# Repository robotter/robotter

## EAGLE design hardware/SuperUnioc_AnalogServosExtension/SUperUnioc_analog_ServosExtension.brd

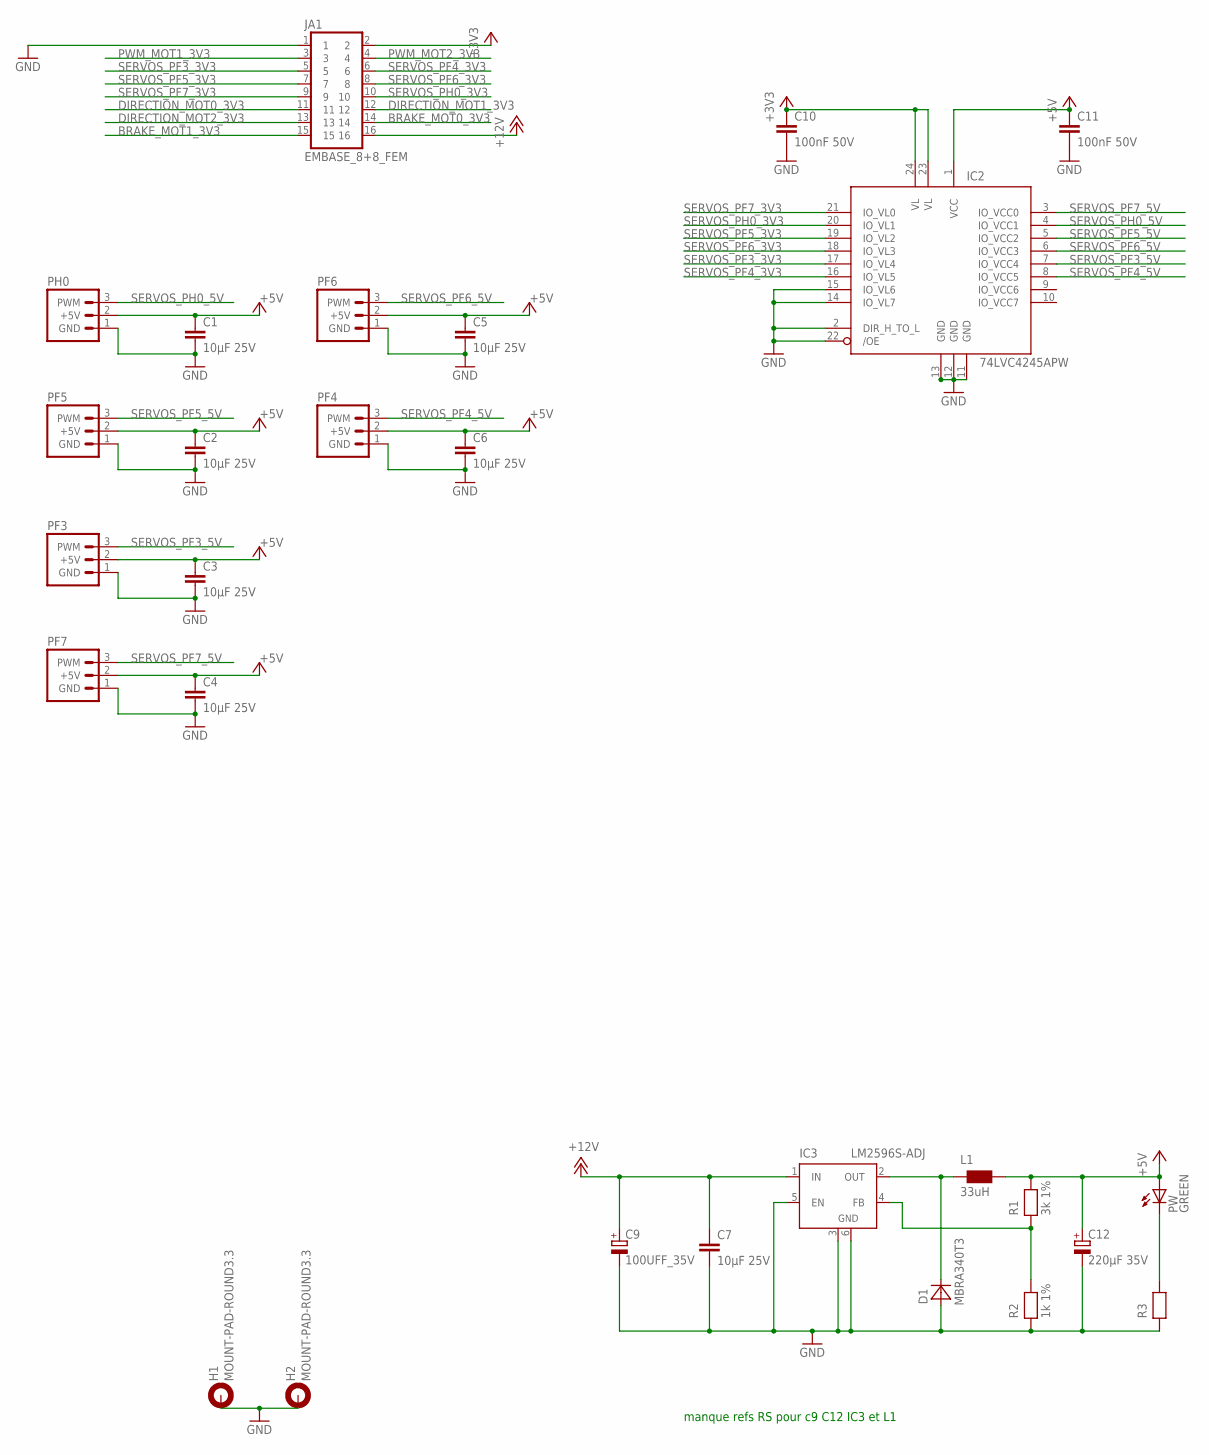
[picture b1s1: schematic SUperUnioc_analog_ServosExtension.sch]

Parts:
C1, C2, C3, C4, C5, C6, C7: 10µF 25V; C1210
C9: 100UFF_35V; PANASONIC_F
C10, C11: 100nF 50V; C0603
C12: 220µF 35V; PANASONIC_F
D1: MBRA340T3; SMA
H1, H2: MOUNT-PAD-ROUND3.3; 3,3-PAD
IC2: 74LVC4245APW; TSSOP24
IC3: LM2596S-ADJ; TO263-5
JA1: EMBASE_8+8_FEM
L1: 33uH; SRR1280
PF3, PF4, PF5, PF6, PF7: ANALOG_SERVO; ANALOG_SERVOS
PH0: ANALOG_SERVO; ANALOG_SERVOS
PW: GREEN; CHIP-LED0805
R1: 3k 1%; R0603
R2: 1k 1%; R0603
R3: 470-F; R0603

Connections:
+3V3: C10.1, IC2.23 (VL), IC2.24 (VL), JA1.2
+5V: C1.1, C2.1, C3.1, C4.1, C5.1, C6.1, C11.1, C12.+, IC2.1 (VCC), L1.2, PF3.2 (+5V), PF4.2 (+5V), PF5.2 (+5V), PF6.2 (+5V), PF7.2 (+5V), PH0.2 (+5V), PW.A, R1.2
+12V: C7.1, C9.+, IC3.1 (IN), JA1.16
BRAKE_MOT0_3V3: JA1.14
BRAKE_MOT1_3V3: JA1.15
DIRECTION_MOT0_3V3: JA1.11
DIRECTION_MOT1_3V3: JA1.12
DIRECTION_MOT2_3V3: JA1.13
GND: C1.2, C2.2, C3.2, C4.2, C5.2, C6.2, C7.2, C9.-, C10.2, C11.2, C12.-, D1.A, H1.B3,3, H2.B3,3, IC2.2 (DIR_H_TO_L), IC2.11 (GND), IC2.12 (GND), IC2.13 (GND), IC2.14 (IO_VL7), IC2.15 (IO_VL6), IC2.22 (/OE), IC3.3 (GND), IC3.5 (EN), IC3.6 (GND), JA1.1, PF3.1 (GND), PF4.1 (GND), PF5.1 (GND), PF6.1 (GND), PF7.1 (GND), PH0.1 (GND), R2.1, R3.1
unnamed: PW.C, R3.2
unnamed: IC3.4 (FB), R1.1, R2.2
unnamed: D1.C, IC3.2 (OUT), L1.1
PWM_MOT1_3V3: JA1.3
PWM_MOT2_3V3: JA1.4
SERVOS_PF3_3V3: IC2.17 (IO_VL4), JA1.5
SERVOS_PF3_5V: IC2.7 (IO_VCC4), PF3.3 (PWM)
SERVOS_PF4_3V3: IC2.16 (IO_VL5), JA1.6
SERVOS_PF4_5V: IC2.8 (IO_VCC5), PF4.3 (PWM)
SERVOS_PF5_3V3: IC2.19 (IO_VL2), JA1.7
SERVOS_PF5_5V: IC2.5 (IO_VCC2), PF5.3 (PWM)
SERVOS_PF6_3V3: IC2.18 (IO_VL3), JA1.8
SERVOS_PF6_5V: IC2.6 (IO_VCC3), PF6.3 (PWM)
SERVOS_PF7_3V3: IC2.21 (IO_VL0), JA1.9
SERVOS_PF7_5V: IC2.3 (IO_VCC0), PF7.3 (PWM)
SERVOS_PH0_3V3: IC2.20 (IO_VL1), JA1.10
SERVOS_PH0_5V: IC2.4 (IO_VCC1), PH0.3 (PWM)

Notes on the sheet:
manque refs RS pour c9 C12 IC3 et L1

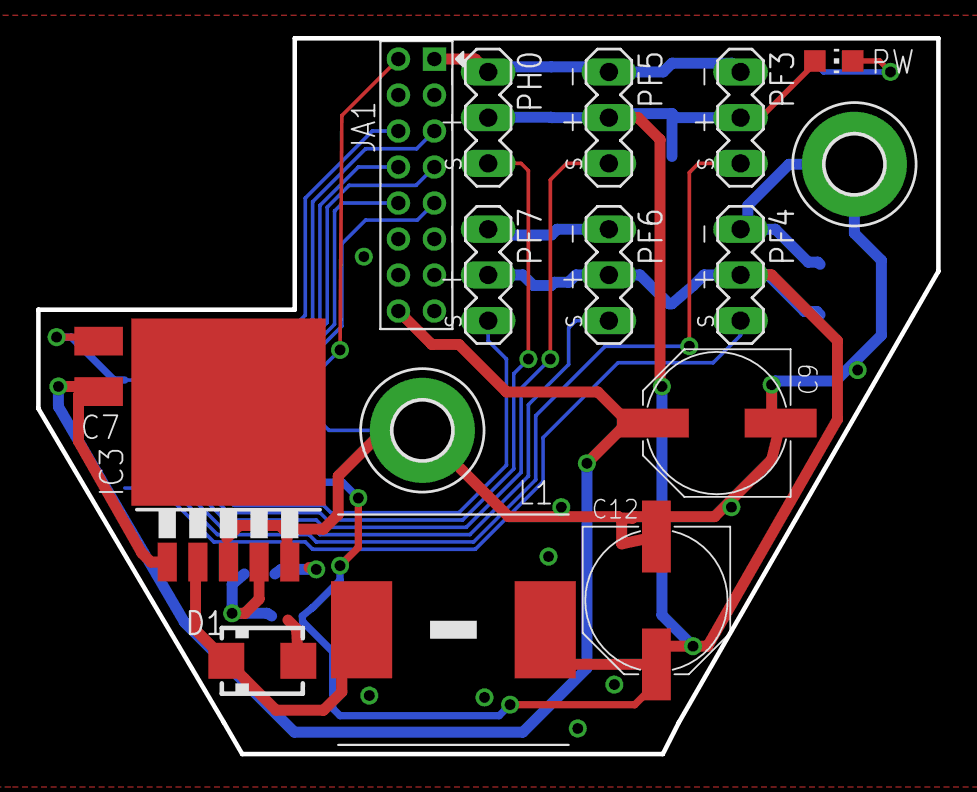
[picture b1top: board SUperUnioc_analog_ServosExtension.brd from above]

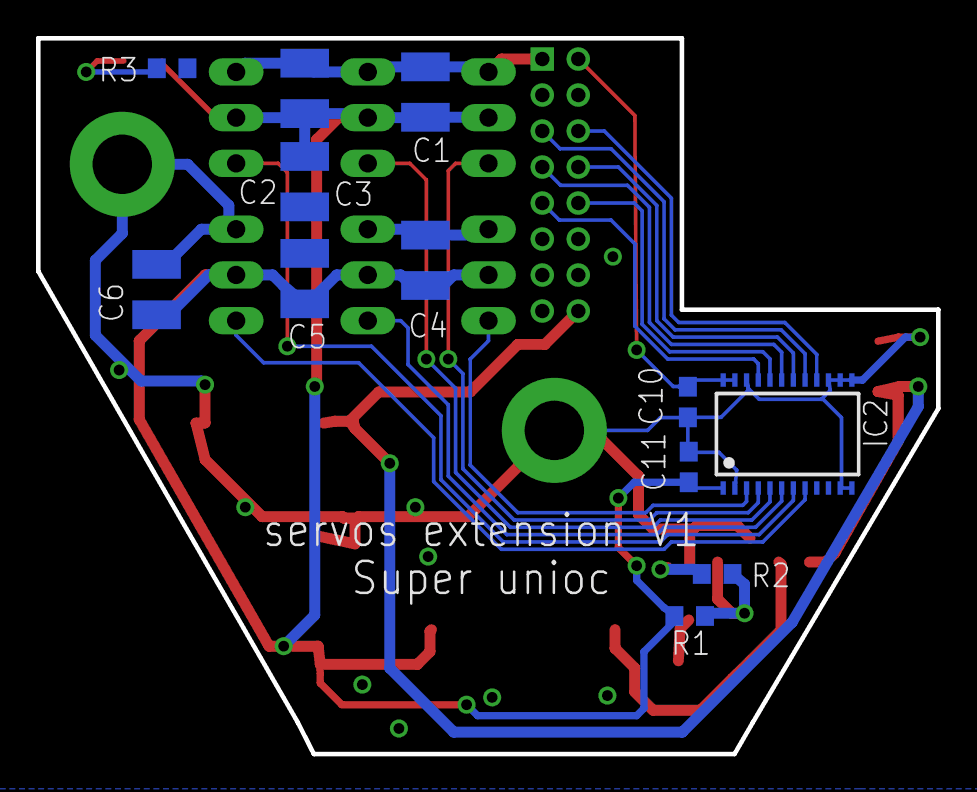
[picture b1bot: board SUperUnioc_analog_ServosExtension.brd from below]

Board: 2 copper layers, 50.0 x 39.8 mm, 28 parts (12 on the bottom side), 19 nets.
